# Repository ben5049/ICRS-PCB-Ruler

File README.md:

# ICRS PCB Ruler

A 15cm PCB ruler designed for Imperial College Robotics Society. It can be easily adapted/rebranded using the KiCad project in this repository.

Front:

Back:

## KiCad Project
To open this project in KiCad 7.0 clone this repository and open the .kicad_pro file in [Ruler_KiCad](Ruler_KiCad). Next open the PCB editor and go to `Preferences > Manage Footprint Libraries > Add Existing` (the folder icon below the list of libraries). Then navigate to `Ruler_KiCad/ruler_footprints` and click "select folder". This is in order to get the custom footprints used in this project.

## Ordering
The gerber files needed for ordering can be found in [Ruler_gerbers.zip](Ruler_KiCad/Ruler_gerbers/Ruler_gerbers.zip). Simply upload this .zip file to any PCB manufacturer's website.

The recommended specifications for ordering this PCB are as follows:
* 2 Layers
* 1.6mm thick FR4
* Blue soldermask
* White silkscreen
* ENIG surface finish
* <= 1 oz Copper weight
* Tented vias (doesn't matter as there are no vias)
* +- 0.2mm Board outline tolerance
* Remove order number

Using [JLCPCB's](https://jlcpcb.com/) pricing, the cost of ordering x number of boards has been plotted in [Pricing.xlsx](Pricing.xlsx).

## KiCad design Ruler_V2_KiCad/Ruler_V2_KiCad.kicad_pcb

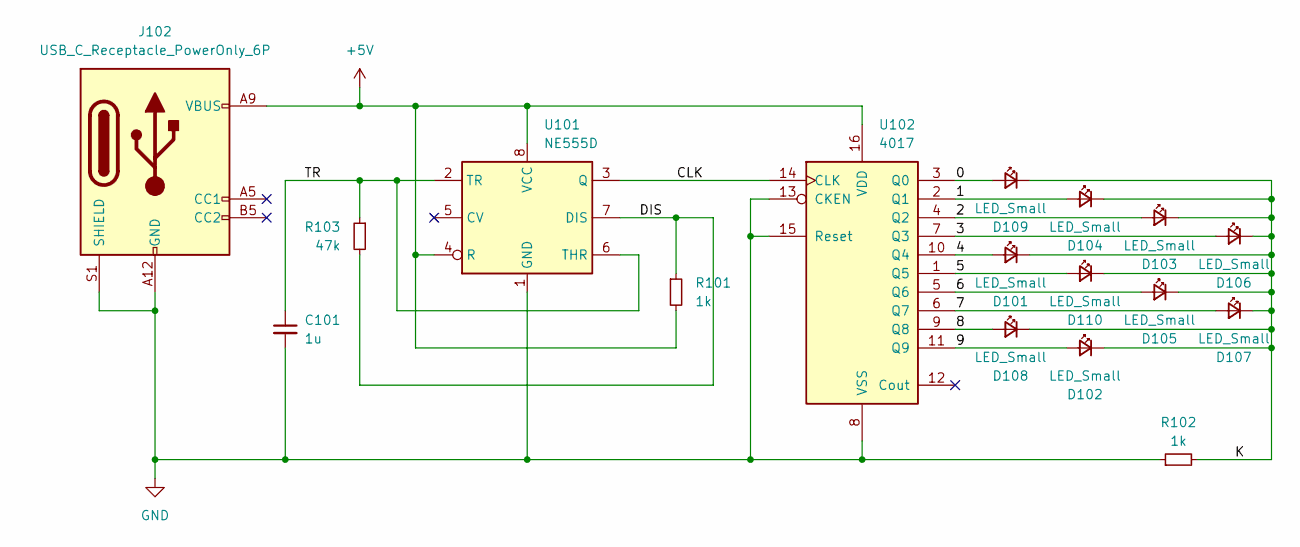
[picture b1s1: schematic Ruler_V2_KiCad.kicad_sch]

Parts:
C101: 1u; C_0402_1005Metric
D101, D102, D103, D104, D105, D106, D107, D108, D109, D110: LED_Small; LED_0402_1005Metric
J102: USB_C_Receptacle_PowerOnly_6P; USB_C_Receptacle_GCT_USB4135-GF-A_6P_TopMnt_Horizontal
R101, R102: 1k; R_0402_1005Metric
R103: 47k; R_0402_1005Metric
U101: NE555D; SOIC-8_3.9x4.9mm_P1.27mm
U102: 4017; SOP-16_3.9x9.9mm_P1.27mm

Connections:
+5V: J102.A9 (VBUS), J102.B9 (VBUS), R101.2, U101.4 (R), U101.8 (VCC), U102.16 (VDD)
/0: D109.2 (A), U102.3 (Q0)
/1: D104.2 (A), U102.2 (Q1)
/2: D103.2 (A), U102.4 (Q2)
/3: D106.2 (A), U102.7 (Q3)
/4: D101.2 (A), U102.10 (Q4)
/5: D110.2 (A), U102.1 (Q5)
/6: D105.2 (A), U102.5 (Q6)
/7: D107.2 (A), U102.6 (Q7)
/8: D108.2 (A), U102.9 (Q8)
/9: D102.2 (A), U102.11 (Q9)
/CLK: U101.3 (Q), U102.14 (CLK)
/DIS: R101.1, R103.2, U101.7 (DIS)
/K: D101.1 (K), D102.1 (K), D103.1 (K), D104.1 (K), D105.1 (K), D106.1 (K), D107.1 (K), D108.1 (K), D109.1 (K), D110.1 (K), R102.2
/TR: C101.1, R103.1, U101.2 (TR), U101.6 (THR)
GND: C101.2, J102.A12 (GND), J102.B12 (GND), J102.S1 (SHIELD), R102.1, U101.1 (GND), U102.8 (VSS), U102.13 (CKEN), U102.15 (Reset)

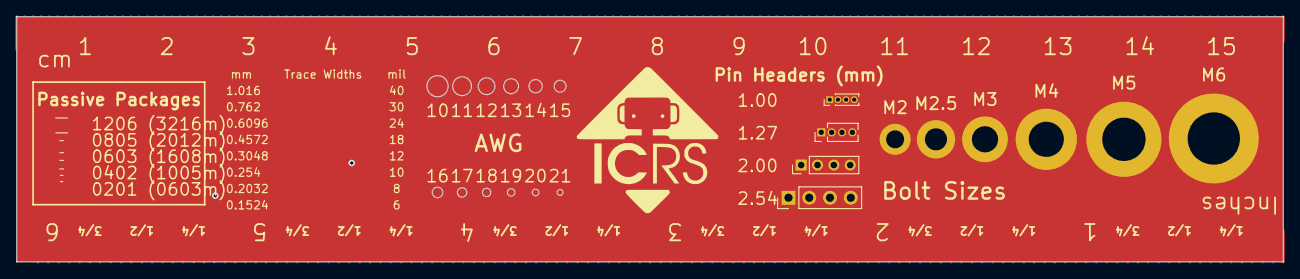
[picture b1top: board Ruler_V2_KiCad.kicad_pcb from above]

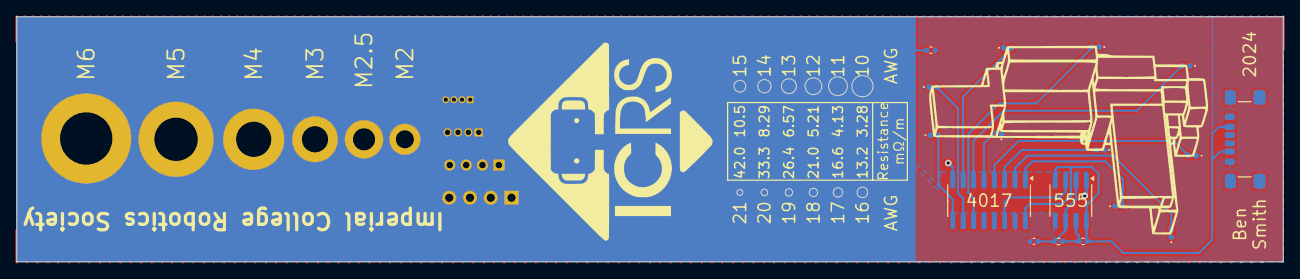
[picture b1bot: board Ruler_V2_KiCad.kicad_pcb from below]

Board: 2 copper layers, 155.0 x 30.0 mm, 17 parts (17 on the bottom side), 16 nets.

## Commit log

2023-08-07 Fixed formatting
2023-08-07 Corrected typo
2023-10-03 Create LICENSE
2024-09-02 Added V2
